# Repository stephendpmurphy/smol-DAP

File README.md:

# smol-DAP
Small form factor DAP-Link programming/debugging board

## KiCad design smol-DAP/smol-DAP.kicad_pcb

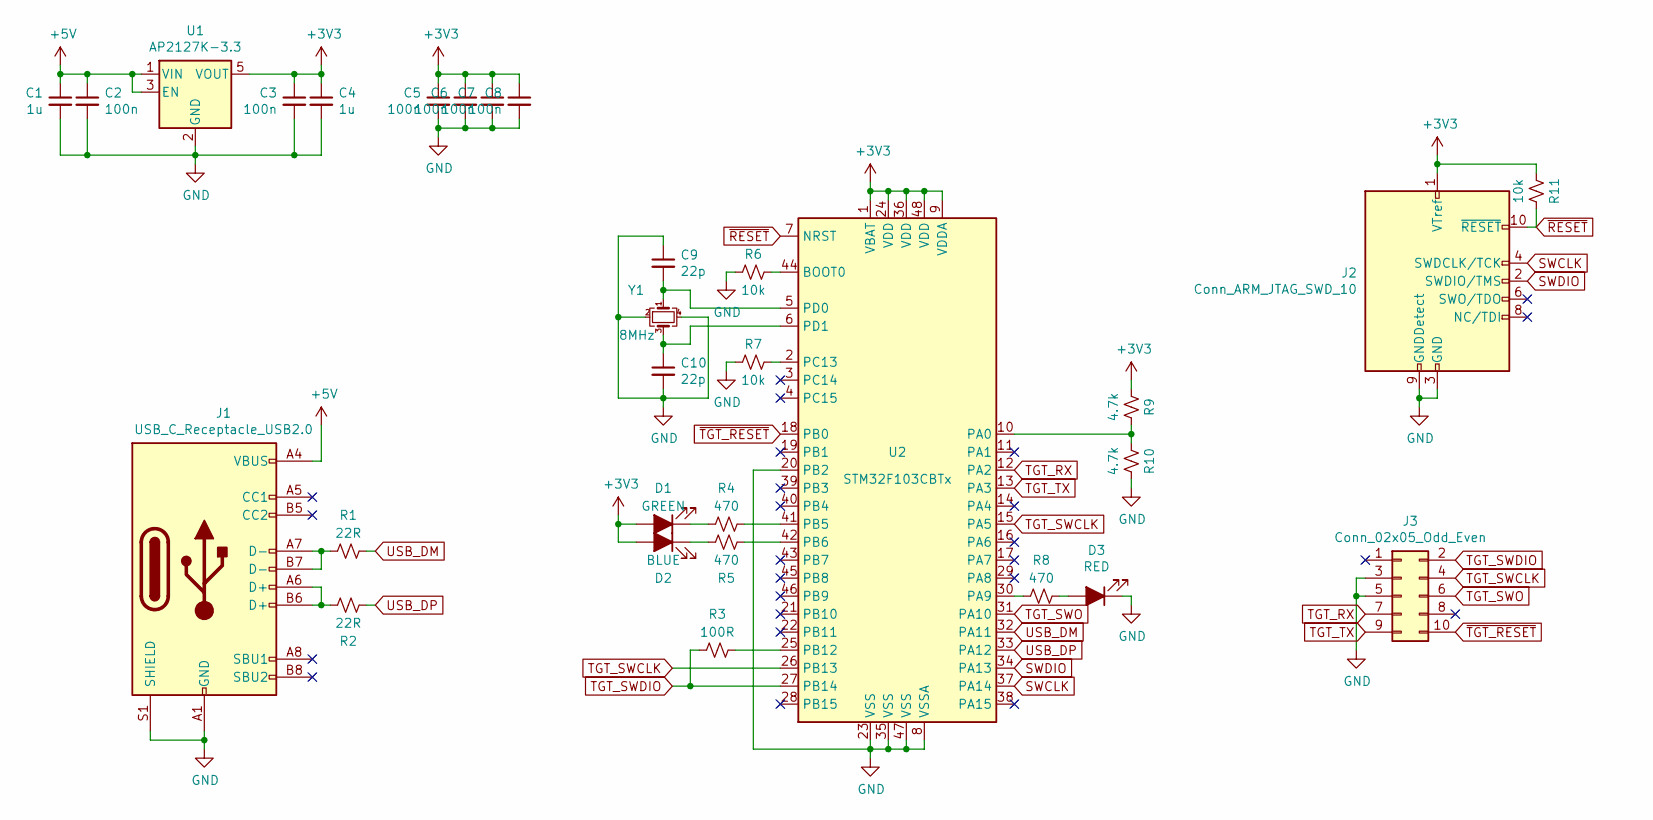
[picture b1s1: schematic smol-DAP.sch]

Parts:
C1, C4: 1u; C_0402_1005Metric
C2, C3, C5, C6, C7, C8: 100n; C_0402_1005Metric
C9, C10: 22p; C_0402_1005Metric
D1: GREEN; LED_0603_1608Metric
D2: BLUE; LED_0603_1608Metric
D3: RED; LED_0603_1608Metric
J1: USB_C_Receptacle_USB2.0; USB_C_Receptacle_GCT_USB4085
J2: Conn_ARM_JTAG_SWD_10; Tag-Connect_TC2050-IDC-NL_2x05_P1.27mm_Vertical
J3: Conn_02x05_Odd_Even; PinHeader_2x05_P1.00mm_Vertical_SMD
R1, R2: 22R; R_0402_1005Metric
R3: 100R; R_0402_1005Metric
R4, R5, R8: 470; R_0402_1005Metric
R6, R7, R11: 10k; R_0402_1005Metric
R9, R10: 4.7k; R_0402_1005Metric
U1: AP2127K-3.3; SOT-23-5
U2: STM32F103CBTx; LQFP-48_7x7mm_P0.5mm
Y1: 8MHz; Crystal_SMD_Abracon_ABM8G-4Pin_3.2x2.5mm

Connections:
+3V3: C3.1, C4.1, C5.1, C6.1, C7.1, C8.1, D1.2 (A), D2.2 (A), J2.1 (VTref), R9.2, R11.2, U1.5 (VOUT), U2.1 (VBAT), U2.9 (VDDA), U2.24 (VDD), U2.36 (VDD), U2.48 (VDD)
+5V: C1.1, C2.1, J1.A4 (VBUS), J1.A9 (VBUS), J1.B4 (VBUS), J1.B9 (VBUS), U1.1 (VIN), U1.3 (EN)
GND: C1.2, C2.2, C3.2, C4.2, C5.2, C6.2, C7.2, C8.2, C9.1, C10.2, D3.1 (K), J1.A1 (GND), J1.A12 (GND), J1.B1 (GND), J1.B12 (GND), J1.S1 (SHIELD), J2.3 (GND), J2.5 (GND), J2.9 (GNDDetect), J3.3, J3.5, R6.2, R7.2, R10.1, U1.2 (GND), U2.8 (VSSA), U2.20 (PB2), U2.23 (VSS), U2.35 (VSS), U2.47 (VSS), Y1.2, Y1.4
unnamed: C9.2, U2.5 (PD0), Y1.1
unnamed: C10.1, U2.6 (PD1), Y1.3
unnamed: D1.1 (K), R4.2
unnamed: D2.1 (K), R5.1
unnamed: D3.2 (A), R8.1
unnamed: J1.A6 (D+), J1.B6 (D+), R2.1
unnamed: J1.A7 (D-), J1.B7 (D-), R1.2
unnamed: R3.1, U2.25 (PB12)
unnamed: R4.1, U2.41 (PB5)
unnamed: R5.2, U2.42 (PB6)
unnamed: R6.1, U2.44 (BOOT0)
unnamed: R7.1, U2.2 (PC13)
unnamed: R8.2, U2.30 (PA9)
unnamed: R9.1, R10.2, U2.10 (PA0)
SWCLK: J2.4 (SWDCLK/TCK), U2.37 (PA14)
SWDIO: J2.2 (SWDIO/TMS), U2.34 (PA13)
TGT_RX: J3.7, U2.12 (PA2)
TGT_SWCLK: J3.4, U2.15 (PA5), U2.26 (PB13)
TGT_SWDIO: J3.2, R3.2, U2.27 (PB14)
TGT_SWO: J3.6, U2.31 (PA10)
TGT_TX: J3.9, U2.13 (PA3)
USB_DM: R1.1, U2.32 (PA11)
USB_DP: R2.2, U2.33 (PA12)
~RESET: J2.10 (~RESET~), R11.1, U2.7 (NRST)
~TGT_RESET: J3.10, U2.18 (PB0)

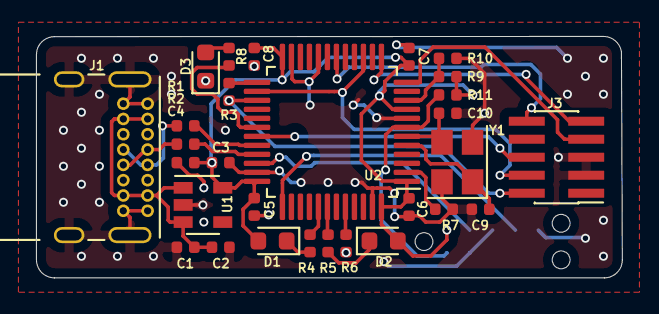
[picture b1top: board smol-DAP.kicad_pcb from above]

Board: 2 copper layers, 32.5 x 13.4 mm, 30 parts (1 on the bottom side), 28 nets.

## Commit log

2020-12-01 initial commit of the smol dap project
2020-12-03 First pass at the smol dap
2020-12-03 Second attempt on the layout. There will be a try #3
2020-12-03 Down to two layers

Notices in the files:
smol-DAP/smol-DAP.kicad_pcb:
cc-by-sa
